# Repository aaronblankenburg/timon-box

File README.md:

# Timon Box

Eine Hörbox für Kinder zum Selberbauen: Figur auflegen, Musik läuft. Ein Druck auf die Seite springt zum nächsten
Titel, ein Drehknopf regelt die Lautstärke. Hörspiele, Lieder und Podcasts kommen über WLAN auf die Box, ohne Cloud
und ohne Konto.

## Was sie kann

- **Token auflegen, Musik läuft.** Jedes Album ist ein gedruckter Token mit NFC-Tag und eigenem Bild. Abnehmen hält
  an, wieder auflegen spielt an derselben Stelle weiter.
- **Für kleine Hände.** Auf die linke Seite drücken heißt zurück, auf die rechte vor. Dazu ein Drehknopf für die
  Lautstärke und eine LED, die zeigt, was die Box gerade tut.
- **Podcasts.** Ein Token kann einem Podcast folgen. Beim Auflegen holt die Box die neueste Folge selbst aus dem Netz.
- **Musik über den Browser.** Mit dem Management-Token öffnet die Box eine Web-Oberfläche. Dort lädt man Titel hoch,
  richtet Podcasts ein und kopiert Alben von einer zweiten Box.
- **Bluetooth-Lautsprecher.** Ein eigener Token macht aus der Box einen Lautsprecher fürs Handy.
- **Akku und USB-C.** Zwei 18650-Zellen, geladen und geflasht über dieselbe Buchse. Ein kleiner Lichtleiter zeigt, ob
  sie lädt, und ein Gurt macht die Box tragbar.

## Selbst bauen

Die Box besteht aus einem 3D-gedruckten Gehäuse, zwei kleinen Platinen und ein paar fertigen Modulen: ESP32,
Verstärker, SD-Karte, RFID-Leser und Lademodul. Man braucht einen 3D-Drucker und einen Lötkolben mit feiner Spitze,
denn einige Bauteile sind SMD in 0805.

**Die Bauanleitung [doc/assembly.pdf](doc/assembly.pdf) führt durch alles** (auf Englisch:
[doc/assembly-en.pdf](doc/assembly-en.pdf)): Teileliste, Platinen bestücken, Gehäuse
drucken, zusammenbauen und die Firmware aufspielen. Jeder Schritt hat ein Bild.

<p align="center">
  
  &nbsp;&nbsp;
  
</p>

| Was | Wo |
|---|---|
| Fertige Druckbetten, eins pro Farbe, für PrusaSlicer und Bambu Studio | [models/plates/](models/plates/) |
| Druckteile einzeln als STL, schon in Druckausrichtung | [models/stl/](models/stl/) |
| Gehäuse und Abstandshalter als STEP | [models/](models/) |
| Platinen: KiCad, Gerber und Schaltpläne | [hardware/](hardware/) |
| Elektronik im Detail | [doc/hardware.md](doc/hardware.md) |

## Firmware aufspielen

Gebaut wird mit [PlatformIO](https://platformio.org), zum Beispiel in VS Code mit der PlatformIO-Erweiterung. Die Box
mit einem Token einschalten, über USB-C an den Rechner stecken, dann:

```bash
git clone https://github.com/aaronblankenburg/timon-box
cd timon-box
pio run -e timon -t upload
```

Die eigene Box bekommt eine eigene Env in der `platformio.ini`: Name, Farbe, die beiden Sondertokens,
Akku-Kalibrierung und Klopfschwellen. Wie man die Werte herausfindet, steht in der Bauanleitung in Kapitel 5.5.

## Tokens basteln

Die Bilder entstehen mit [tools/token-sheet.html](tools/token-sheet.html): im Browser öffnen, sechs Bilder wählen und
zuschneiden, als Fotoabzug 10 × 15 cm bestellen. Ausgeschnitten kommen sie mit doppelseitigem Klebeband auf die
Tokens. Die Tokens selbst sind gedruckt, der NFC-Tag kommt während des Drucks hinein. Fürs Handy gibt es die Seite auch
als Android-App in [android/](android/).

## Mehr lesen

| Datei | Inhalt |
|---|---|
| [doc/usage.md](doc/usage.md) | Bedienung: Tokens, LED, Musik hochladen, Podcasts, Bluetooth |
| [doc/assembly.pdf](doc/assembly.pdf) | Bauanleitung: Elektronik, Druck und Zusammenbau, auf Englisch [doc/assembly-en.pdf](doc/assembly-en.pdf) |
| [doc/hardware.md](doc/hardware.md) | Elektronik: Teile, Platinen, Verkabelung, Inbetriebnahme |
| [doc/architecture.md](doc/architecture.md) | Firmware Modul für Modul |
| [doc/development.md](doc/development.md) | Entwickeln: Klopfsensoren, Podcast-Technik, Tests, Android-App |
| [doc/state-machine.html](doc/state-machine.html) | Zustände der Firmware als Diagramm |
| [CLAUDE.md](CLAUDE.md) | Kurzfassung für die Arbeit mit Claude Code |

## Lizenz

Nachbauen, verändern und weitergeben ist ausdrücklich erwünscht, Geld verdienen damit nicht. Gehäuse, Platinen und
Doku stehen deshalb unter [CC BY-NC-SA 4.0](https://creativecommons.org/licenses/by-nc-sa/4.0/deed.de), Firmware und
Werkzeuge unter der [GPL-3.0](https://www.gnu.org/licenses/gpl-3.0.html). Was genau wofür gilt, steht in
[LICENSE.md](LICENSE.md). Wer die Box kommerziell nutzen möchte, etwa als Bausatz, fragt bitte vorher über ein Issue.

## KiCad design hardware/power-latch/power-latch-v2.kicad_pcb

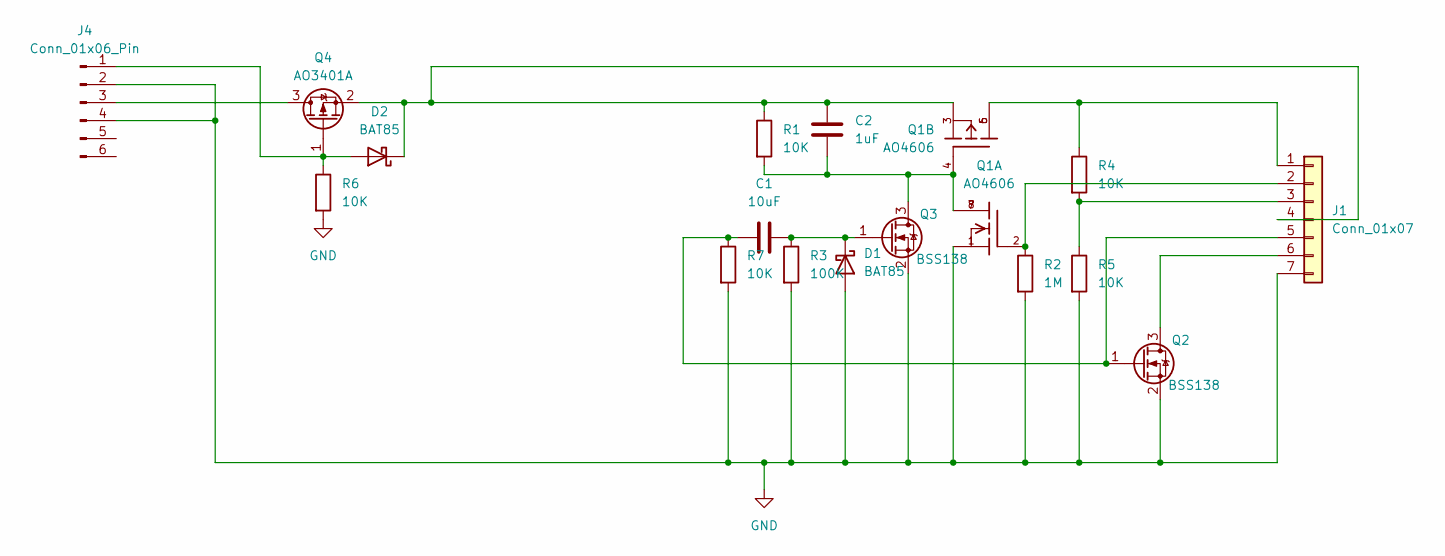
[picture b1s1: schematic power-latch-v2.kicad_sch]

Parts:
C1: 10uF; C_0805_2012Metric_Pad1.18x1.45mm_HandSolder
C2: 1uF; C_0805_2012Metric_Pad1.18x1.45mm_HandSolder
D1: BAT85; D_SOD-323_HandSoldering
D2: BAT85; D_DO-35_SOD27_P7.62mm_Horizontal
J1: Conn_01x07; PinHeader_1x07_P2.54mm_Vertical
J4: Conn_01x06_Pin; TP4056-18650
Q1: AO4606; SOIC-8_3.9x4.9mm_P1.27mm
Q2, Q3: BSS138; SOT-23
Q4: AO3401A; SOT-23
R1, R4, R5, R6, R7: 10K; R_0805_2012Metric_Pad1.20x1.40mm_HandSolder
R2: 1M; R_0805_2012Metric_Pad1.20x1.40mm_HandSolder
R3: 100K; R_0805_2012Metric_Pad1.20x1.40mm_HandSolder

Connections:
GND: D1.2 (A), J1.7, J4.2, J4.4, Q1.1, Q2.2 (S), Q3.2 (S), R2.2, R3.2, R5.2, R6.2, R7.2
unnamed: C1.2, D1.1 (K), Q3.1 (G), R3.1
unnamed: D2.2 (A), J4.1, Q4.1 (G), R6.1
unnamed: C2.2, D2.1 (K), J1.4, Q1.3, Q4.2 (S), R1.1
unnamed: J1.1, Q1.5, Q1.6, R4.1
unnamed: J1.2, Q1.2, R2.1
unnamed: J1.3, R4.2, R5.1
unnamed: C1.1, J1.5, Q2.1 (G), R7.1
unnamed: J1.6, Q2.3 (D)
unnamed: J4.3, Q4.3 (D)
unnamed: C2.1, Q1.4, Q1.7, Q1.8, Q3.3 (D), R1.2

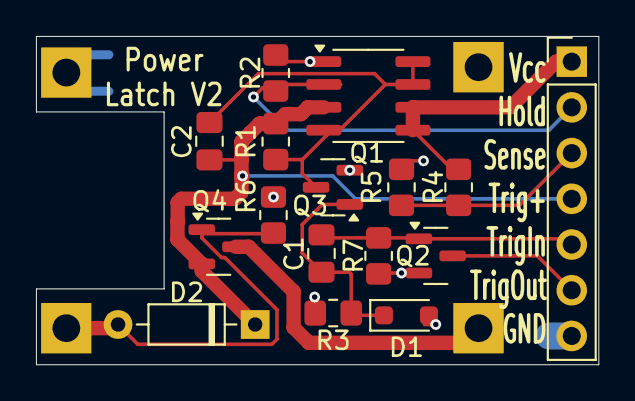
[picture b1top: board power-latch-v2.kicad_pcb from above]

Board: 2 copper layers, 31.2 x 18.2 mm, 17 parts (1 on the bottom side), 11 nets.

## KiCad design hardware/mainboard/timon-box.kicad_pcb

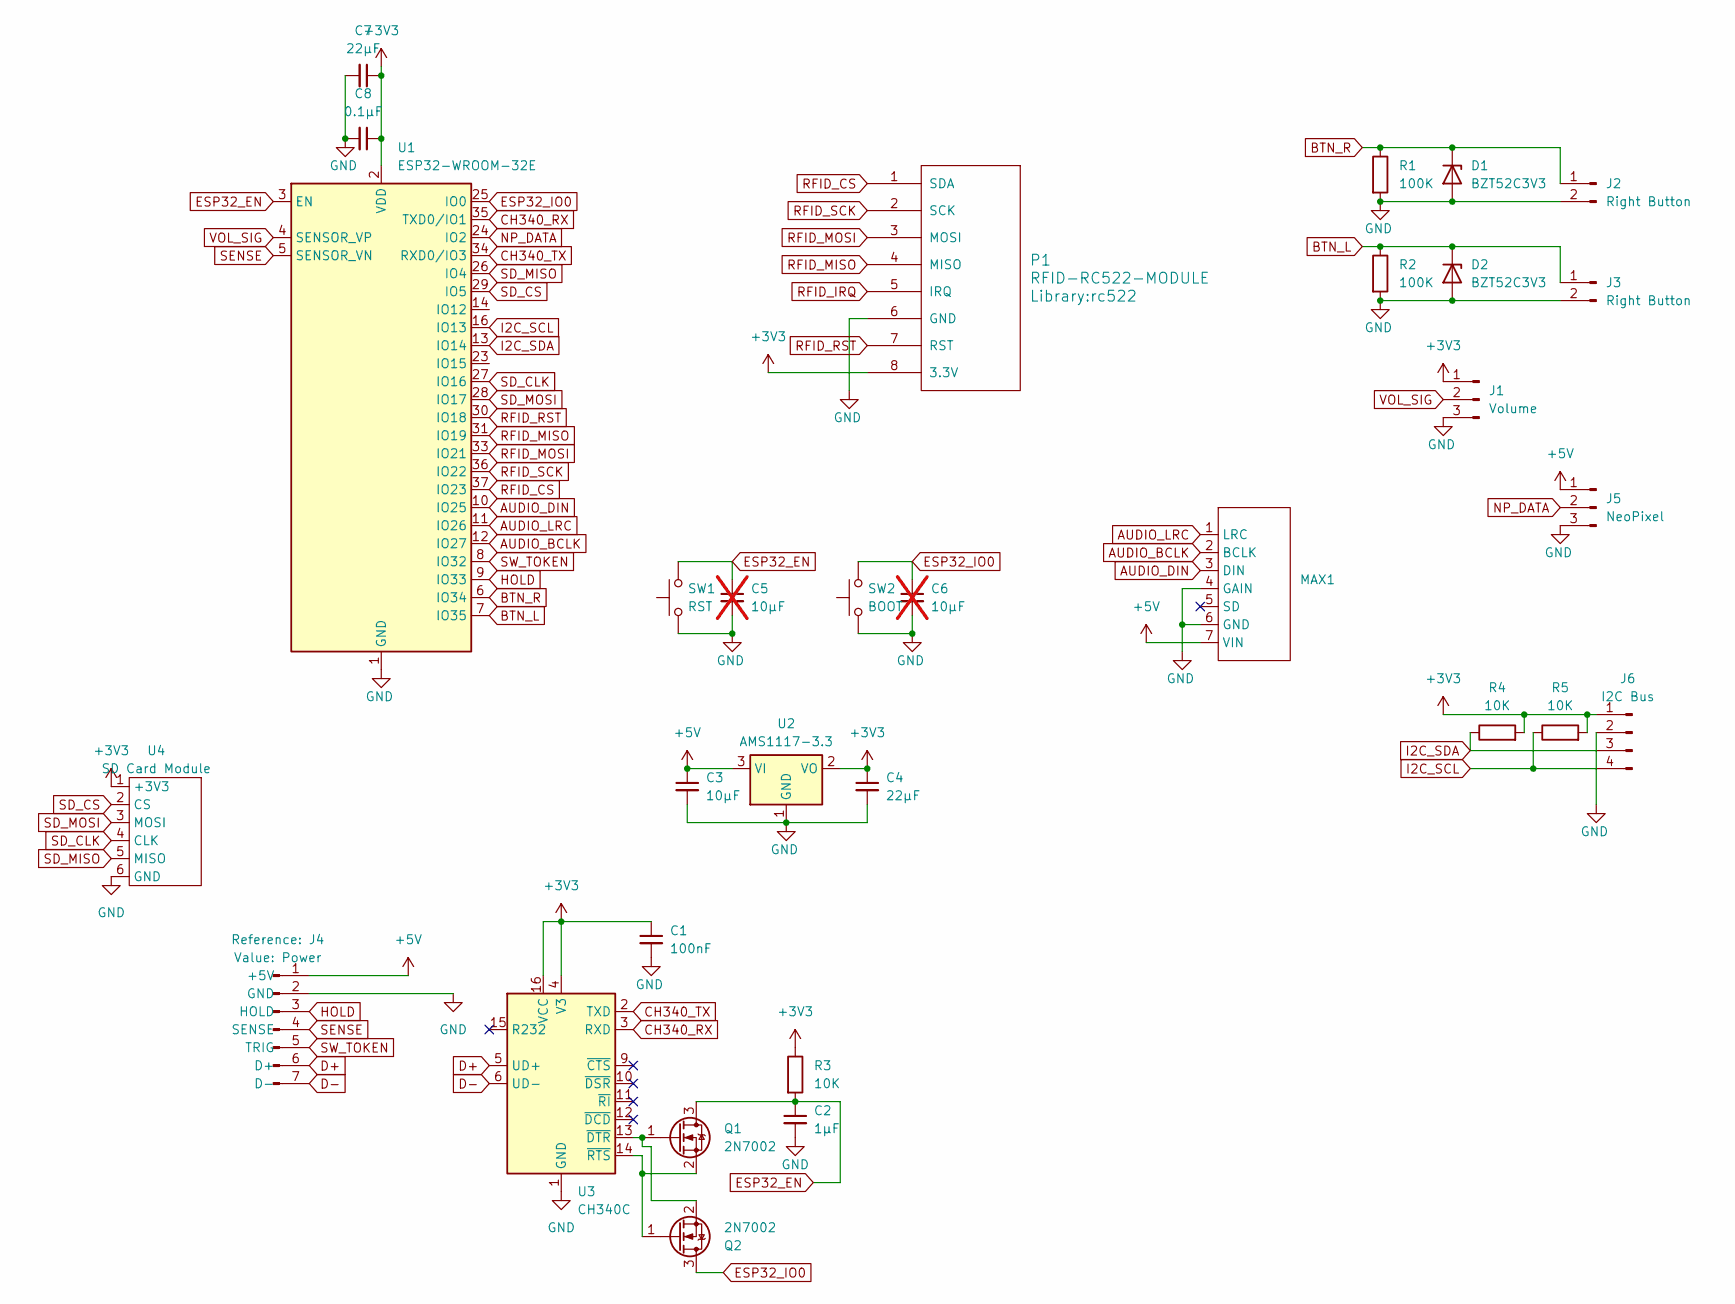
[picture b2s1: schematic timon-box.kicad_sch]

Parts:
C1: 100nF; C_0805_2012Metric
C2: 1µF; C_0805_2012Metric
C3: 10µF; C_0805_2012Metric
C4, C7: 22µF; C_1206_3216Metric
C5, C6: 10µF; C_0805_2012Metric; not fitted
C8: 0.1µF; C_0805_2012Metric
D1, D2: BZT52C3V3; D_SOD-323_HandSoldering
J1: Volume; PinHeader_1x03_P2.54mm_Vertical
J2, J3: Right Button; PinHeader_1x02_P2.54mm_Vertical
J4: Power; PinHeader_1x07_P2.54mm_Vertical
J5: NeoPixel; PinHeader_1x03_P2.54mm_Vertical
J6: I2C Bus; PinHeader_1x04_P2.54mm_Vertical
MAX1: max98357
P1: RFID-RC522-MODULE; rc522
Q1, Q2: 2N7002; SOT-23
R1, R2: 100K; R_0805_2012Metric
R3, R4, R5: 10K; R_0805_2012Metric
SW1: RST; SW_SPST_PTS645
SW2: BOOT; SW_SPST_PTS645
U1: ESP32-WROOM-32E; ESP32-WROOM-32D
U2: AMS1117-3.3; SOT-223-3_TabPin2
U3: CH340C; SOIC-16_3.9x9.9mm_P1.27mm
U4: SD Card Module; sdcard-module

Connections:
+3V3: C1.1, C4.1, C7.1, C8.1, J1.1, J6.1, P1.8 (3.3V), R3.1, R4.2, R5.2, U1.2 (VDD), U2.2 (VO), U3.4 (V3), U3.16 (VCC), U4.1 (+3V3)
+5V: C3.1, J4.1 (+5V), J5.1, MAX1.7 (VIN), U2.3 (VI)
AUDIO_BCLK: MAX1.2 (BCLK), U1.12 (IO27)
AUDIO_DIN: MAX1.3 (DIN), U1.10 (IO25)
AUDIO_LRC: MAX1.1 (LRC), U1.11 (IO26)
BTN_L: D2.1 (K), J3.1, R2.1, U1.7 (IO35)
BTN_R: D1.1 (K), J2.1, R1.1, U1.6 (IO34)
CH340_RX: U1.35 (TXD0/IO1), U3.3 (RXD)
CH340_TX: U1.34 (RXD0/IO3), U3.2 (TXD)
D+: J4.6 (D+), U3.5 (UD+)
D-: J4.7 (D-), U3.6 (UD-)
ESP32_EN: C2.1, C5.1, Q1.3 (D), R3.2, SW1.2, U1.3 (EN)
ESP32_IO0: C6.1, Q2.3 (D), SW2.2, U1.25 (IO0)
GND: C1.2, C2.2, C3.2, C4.2, C5.2, C6.2, C7.2, C8.2, D1.2 (A), D2.2 (A), J1.3, J2.2, J3.2, J4.2 (GND), J5.3, J6.2, MAX1.4 (GAIN), MAX1.6 (GND), P1.6 (GND), R1.2, R2.2, SW1.1, SW2.1, U1.1 (GND), U1.15 (GND), U1.38 (GND), U1.39 (GND), U2.1 (GND), U3.1 (GND), U4.6 (GND)
HOLD: J4.3 (HOLD), U1.9 (IO33)
I2C_SCL: J6.4, R5.1, U1.16 (IO13)
I2C_SDA: J6.3, R4.1, U1.13 (IO14)
NP_DATA: J5.2, U1.24 (IO2)
unnamed: Q1.1 (G), Q2.2 (S), U3.13 (~DTR)
unnamed: Q1.2 (S), Q2.1 (G), U3.14 (~RTS)
RFID_CS: P1.1 (SDA), U1.37 (IO23)
RFID_IRQ: P1.5 (IRQ)
RFID_MISO: P1.4 (MISO), U1.31 (IO19)
RFID_MOSI: P1.3 (MOSI), U1.33 (IO21)
RFID_RST: P1.7 (RST), U1.30 (IO18)
RFID_SCK: P1.2 (SCK), U1.36 (IO22)
SD_CLK: U1.27 (IO16), U4.4 (CLK)
SD_CS: U1.29 (IO5), U4.2 (CS)
SD_MISO: U1.26 (IO4), U4.5 (MISO)
SD_MOSI: U1.28 (IO17), U4.3 (MOSI)
SENSE: J4.4 (SENSE), U1.5 (SENSOR_VN)
SW_TOKEN: J4.5 (TRIG), U1.8 (IO32)
VOL_SIG: J1.2, U1.4 (SENSOR_VP)

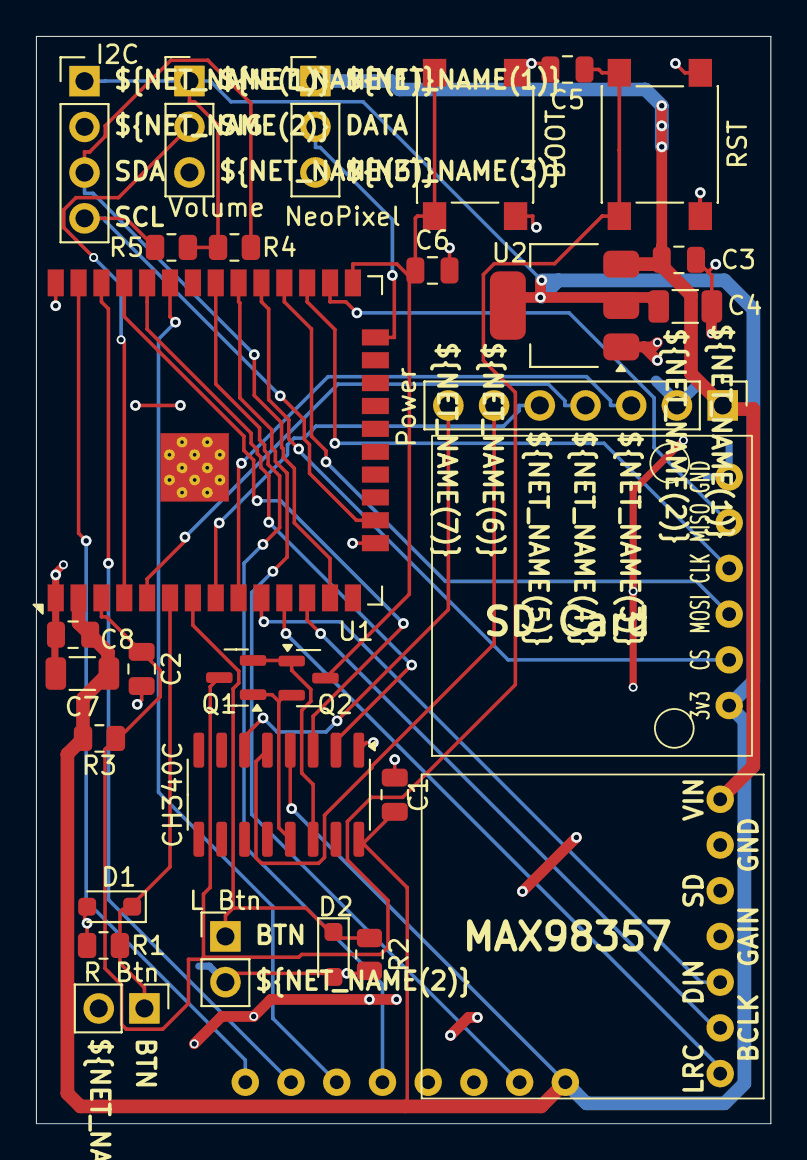
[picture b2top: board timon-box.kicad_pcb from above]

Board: 2 copper layers, 40.8 x 60.4 mm, 31 parts (1 on the bottom side), 32 nets.

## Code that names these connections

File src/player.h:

#ifndef PLAYER_CLASS
#define PLAYER_CLASS

#include "Arduino.h"
#include "Audio.h"
#include "FS.h"
#include "LList.h"
#include "SD.h"
#include "management-server.h"

// SD card
#define SD_SPEED 27000000
#define SD_CS GPIO_NUM_5
#define SD_MOSI GPIO_NUM_17
#define SD_SCK GPIO_NUM_16
#define SD_MISO GPIO_NUM_4

#define I2S_DOUT 25
#define I2S_BCLK GPIO_NUM_27  // I2S
#define I2S_LRC GPIO_NUM_26

#define LAST_PLAYED_FILE_NAME "/last_played.txt"
#define INDEX_FILE_NAME "/index.txt"

class Player {
 private:
  SPIClass spiSD = SPIClass(HSPI);
  String albumDir;
  LList<String> playlist;

  int playlistIndexOf(String track) {
    for (size_t i = 0; i < playlist.size(); i++) {
      if (playlist.get(i) == track) return i;
    }
    return -1;
  }

  void startSdCard() {
    spiSD.begin(SD_SCK, SD_MISO, SD_MOSI, SD_CS);
    if (!SD.begin(SD_CS, spiSD, SD_SPEED)) {
      Serial.println("Error talking to SD card!");
      sdConnected = false;
    } else {
      sdConnected = true;
    }
  }

  void playFile(String path) {
    // startSdCard();
    if (SD.exists(path)) {
      handleParams(path);
      currentlyPlayingFile = path;
      sdConnected = audio.connecttoSD(path.c_str());
      Serial.println("playing file: " + path);
    } else {
      Serial.println("file does not exist, flushing player cache: " + path);
      flushPlayerCache();
      loadAlbumDirIntoPlaylist(albumDir);
      startOrContinueAlbum();
    }
  }

  void flushPlayerCache() {
    if (SD.exists(albumDir + LAST_PLAYED_FILE_NAME)) SD.remove(albumDir + LAST_PLAYED_FILE_NAME);
    if (SD.exists(albumDir + INDEX_FILE_NAME)) SD.remove(albumDir + INDEX_FILE_NAME);
  }

  /**
   * handle params in filename submitted as param[value]
   * supported param: vol with value between 0 and 21
   */
  void handleParams(String path) {
    int maxVolStart = path.indexOf("vol[") + 4;

    if (maxVolStart > -1) {
      String m = path.substring(maxVolStart);
      this->songMaxVolume = m.substring(0, m.indexOf("]")).toInt();
      Serial.print("Set songMaxVolume to ");
      Serial.println(this->songMaxVolume);
    } else {
      this->songMaxVolume = 0;
    }
  }

  void loadAlbumIntoPlaylist(String albumDir) {
    String indexFilePath = albumDir + INDEX_FILE_NAME;
    if (SD.exists(indexFilePath)) {
      Serial.println("Load index file");
      loadAlbumIndexIntoPlaylist(indexFilePath);
    } else {
      Serial.println("Load album from dir and create index file");
      loadAlbumDirIntoPlaylist(albumDir);
      savePlaylistToAlbumIndex(indexFilePath);
    }
  }

  void loadAlbumIndexIntoPlaylist(String indexFilePath) {
    File file = SD.open(albumDir + INDEX_FILE_NAME);

    String fileName;
    while (file.available()) {
      fileName = file.readStringUntil('\n');
      fileName.trim();
      playlist.add(fileName);
    }
    file.close();

    if (playlist.size() == 0) {
      Serial.println("Index empty, fallback to read from dir");
      loadAlbumDirIntoPlaylist(albumDir);
      savePlaylistToAlbumIndex(indexFilePath);
    }
  }

  void savePlaylistToAlbumIndex(String indexFilePath) {
    File file = SD.open(indexFilePath, FILE_WRITE);
    if (!file) {
      Serial.println("Failed to open album index file for writing");
      return;
    }
    Serial.println("Saving playlist with size " + playlist.size());
    for (uint8_t i = 0; i < playlist.size(); i++) {
      file.println(playlist[i]);
    }
    Serial.println("Index saved to " + indexFilePath);
    file.close();
  }

  void loadAlbumDirIntoPlaylist(String albumDir) {
    File album = SD.open(albumDir);
    File file = album.openNextFile();

    while (file) {
      if (!file.isDirectory() && String(file.name()).endsWith(".mp3")) {
        playlist.add(albumDir + "/" + file.name());
      }
      file = album.openNextFile();
    }
    playlist.sort([](String &a, String &b) { return a.compareTo(b); });
  }

 public:
  Audio audio = Audio();
  boolean sdConnected = false;
  unsigned int songMaxVolume = 0;
  String currentlyPlayingFile;

  Player() {}

  void setup() {
    startSdCard();
    audio.setPinout(I2S_BCLK, I2S_LRC, I2S_DOUT);
    audio.forceMono(true);
  }

  void setupManagementServer(String tag) {
    audio.~Audio();
    playlist.~LList();
    determineAlbumDir(tag);
    setupWebServer(this->albumDir);
  }

  void loop() { audio.loop(); }

  void determineAlbumDir(String tag) {
    albumDir = "";
    File root = SD.open("/");
    File file = root.openNextFile();
    while (file) {
      Serial.print(file.name());
      Serial.print("  ");
      Serial.print(String(file.name()));
      Serial.print("  ");
      Serial.println(file.isDirectory());
      if (file.isDirectory() && String(file.name()).endsWith(tag)) {
        albumDir = file.name();
        albumDir = "/" + albumDir;
        break;
      }
      file = root.openNextFile();
    }

    Serial.println("albumDir: " + albumDir);

    if (albumDir == "") {
      albumDir = "/" + tag;
      Serial.println("New tag, created dir " + tag);
      SD.mkdir(albumDir);
    }
  }

  void loadPlaylist(String tag) {
    playlist.clear();
    currentlyPlayingFile = "";

    determineAlbumDir(tag);

    loadAlbumIntoPlaylist(albumDir);
  }

  void startOrContinueAlbum() {
    if (playlist.size() > 0) {
      playFile(getLastPlayedSong());
    } else {
      Serial.println("playlist empty");
    }
  }

  void resume() {
    if (!audio.isRunning()) audio.pauseResume();
  }

  void pause() {
    if (audio.isRunning()) audio.pauseResume();
  }

  void next() {
    int currentIndex = playlistIndexOf(currentlyPlayingFile);
    if (currentIndex == playlist.size() - 1) {
      playFile(playlist.get(0));
    } else {
      playFile(playlist.get(currentIndex + 1));
    }
  }

  void previous() {
    if (audio.getAudioCurrentTime() <= 5) {
      int currentIndex = playlistIndexOf(currentlyPlayingFile);
      if (currentIndex == 0) {
        playFile(playlist.get(playlist.size() - 1));
      } else {
        playFile(playlist.get(currentIndex - 1));
      }
    } else {
      // after 5 sec just restart file
      playFile(currentlyPlayingFile);
    }
  }

  String getLastPlayedSong() {
    if (!SD.exists(albumDir + LAST_PLAYED_FILE_NAME)) {
      Serial.println("Failed to open file for reading");
      return playlist.get(0);
    }

    File file = SD.open(albumDir + LAST_PLAYED_FILE_NAME);

    String fileName;
    while (file.available()) {
      fileName += (char)file.read();
    }
    file.close();

    if (SD.exists(fileName)) {
      return fileName;
    } else {
      return playlist.get(0);
    }
  }

  void savePlayingState() {
    File file = SD.open(albumDir + LAST_PLAYED_FILE_NAME, FILE_WRITE);
    if (!file) {
      Serial.println("Failed to open file for writing");
      return;
    }
    if (file.print(currentlyPlayingFile)) {
      Serial.println("Last played song saved");
    }
    file.close();
  }

  void playClick() {
    this->songMaxVolume = 0;
    Serial.println("playing click");
    audio.stopSong();
    sdConnected = audio.connecttoSD("/tap.mp3");
    unsigned long startTime = millis();
    while (millis() < startTime + 300) loop();
  }

  void playAlert() {
    this->songMaxVolume = 0;
    Serial.println("playing alert");
    audio.stopSong();
    sdConnected = audio.connecttoSD("/alert.mp3");
    unsigned long startTime = millis();
    while (millis() < startTime + 4500) loop();
  }

  void printPlaylist() {
    Serial.println("index: song name");
    Serial.println("----------------");
    for (size_t i = 0; i < playlist.size(); i++) {
      audio.loop();
      String songPath = playlist.get(i);
      String songName = songPath.substring(songPath.lastIndexOf('/') + 1);
      songName.replace('_', ' ');
      Serial.print(i);
      Serial.print(": ");
      Serial.println(songName);
    }
  }

  void playSongByIndex(int index) {
    if (index < 0) {
      Serial.println("index < 0");
      return;
    }
    if (index >= playlist.size()) {
      Serial.println("index too large");
      return;
    }

    playFile(playlist.get(index));
  }
};

#endif

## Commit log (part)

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2025-01-01 init
2025-01-02 extend state machine with management tag
2025-01-02 style file list
2025-01-02 upload with progress indicator using local ap
2025-01-02 add styling a and folder rename option
2025-01-03 add redirect dns
2025-01-04 change /delete to post
2025-01-04 ensure file list is sorted
2025-01-05 add pagination, separate page for files and load dir in advance
2025-01-06 save ram by using printf and destruct audio and playlist before server start
2025-01-07 styling
2025-01-08 upload to /temp first, then rename
2025-01-08 improve styling and performance
2025-01-10 fix filename sanitizing, renaming and add buttons for song selection
2025-01-10 do not list index and last played file
2025-01-15 start with list page on /
2025-01-15 extract base class from player.h
2025-03-18 add token script
2025-03-18 add bt player class
2025-04-06 Changes to be committed: new file: .vscode/tasks.json# modified: README.md new file: assets/hw_bat.jpeg new file: assets/hw_connector.jpeg new file: assets/hw_cutpcb.jpeg new file: assets/hw_hack.jpe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
2025-04-06 Update Architecture
2025-04-22 handle empty last_played.txt
2025-04-22 use gpio 32 for token detection
2025-06-19 improve battery reading via lowpass filter and add neo pixel for state visualization
2025-06-22 reduce rfid antenna gain to read tags more reliably
2025-07-28 upgrade dependencies
2025-07-28 parameterize build envs
2025-07-28 fix low battery audio warning and led
2025-07-28 stabelize neo pixel
2025-07-29 fix wrong red led after each song
2025-08-06 pull up POWER_SUPPLY_PIN as early as possible
2025-08-06 downgrade audioI2S version to fix mp3 playback bug
2025-08-06 skip bootloader validation to speed up start
2025-08-08 use pull up on power supply pin
2025-10-16 add low pass filter for knock sensor to filter hf noise from speaker
2025-10-16 reduce thresholds for right and left sensor
2025-10-16 reduce circle diameter of token to 44.5mm
2025-10-17 optimize knock low pass filter
